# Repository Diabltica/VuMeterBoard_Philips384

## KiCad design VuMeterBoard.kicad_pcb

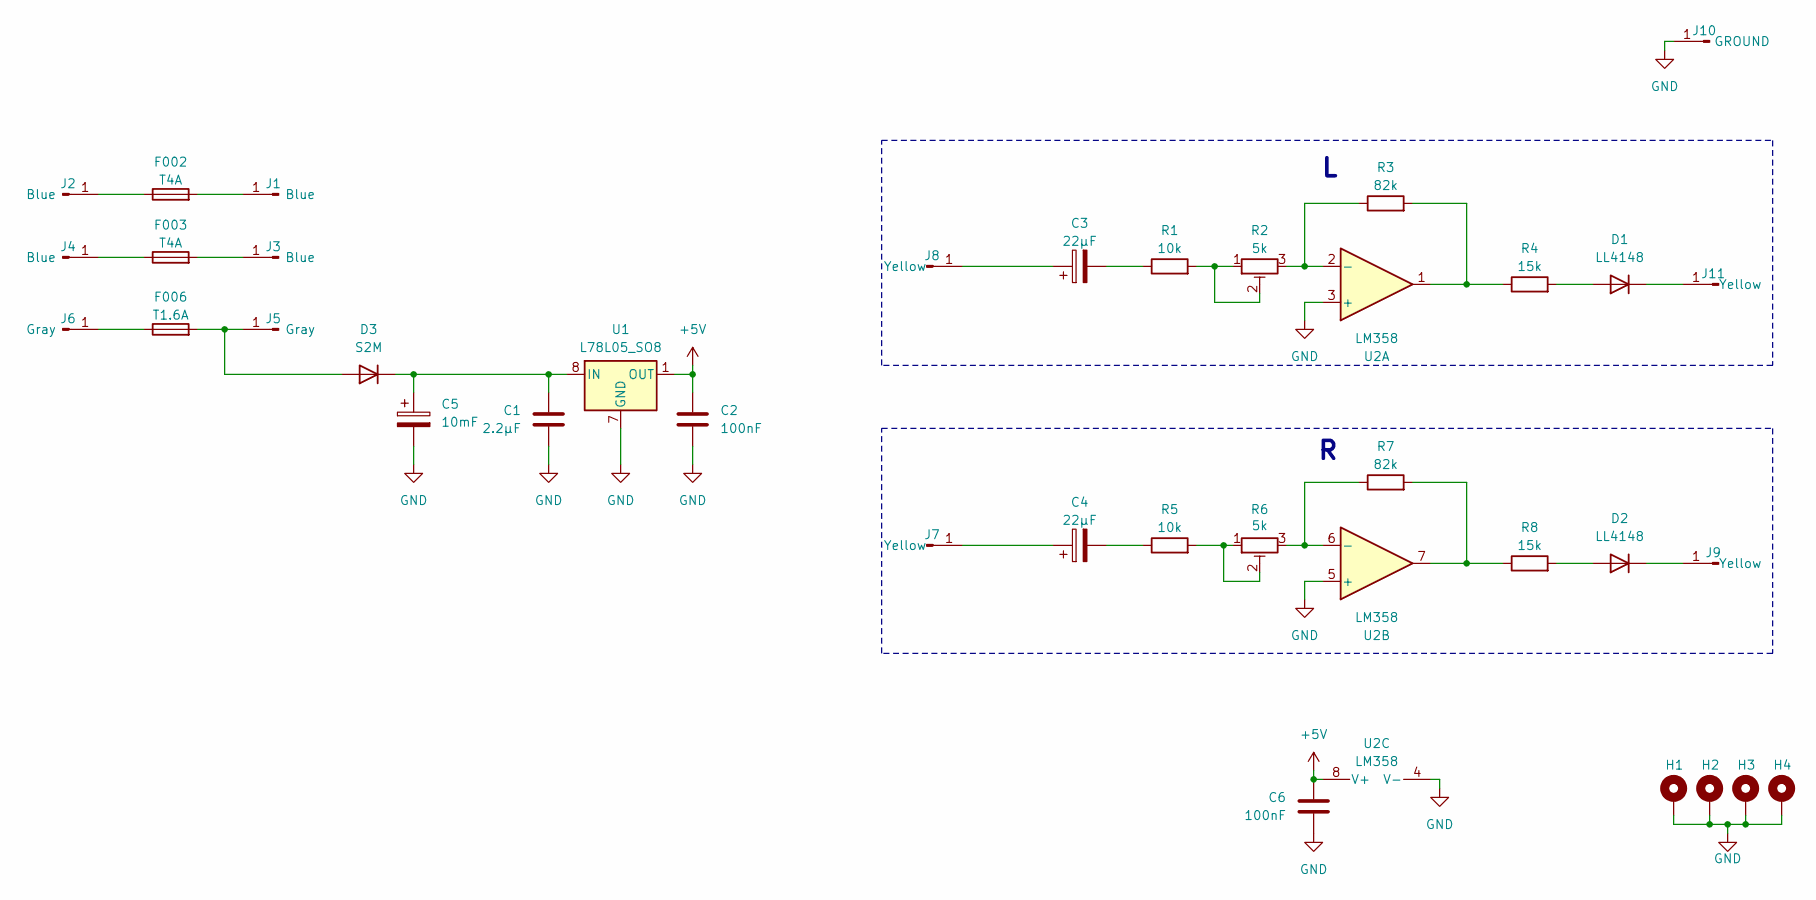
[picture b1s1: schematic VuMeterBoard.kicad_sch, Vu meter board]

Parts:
C1: 2.2µF; C_0603_1608Metric
C2, C6: 100nF; C_0603_1608Metric
C3, C4: 22µF; CP_Elec_6.3x7.7
C5: 10mF; CP_Radial_D18.0mm_P7.50mm
D1, D2: LL4148; D_MiniMELF
D3: S2M; D_SMB
F002, F003: T4A; Fuseholder_Cylinder-5x20mm_Stelvio-Kontek_PTF78_Horizontal_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
F006: T1.6A; Fuseholder_Cylinder-5x20mm_Stelvio-Kontek_PTF78_Horizontal_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
H1, H2, H3, H4: MountingHole_Pad; MountingHole_3.2mm_M3_Pad_Via
J1, J2, J3, J4, J5, J6, J7, J8, J9, J10, J11: Conn_01x01_Pin; PinHeader_1x01_P2.54mm_Vertical
R1, R5: 10k; R_0603_1608Metric
R2, R6: 5k; Potentiometer_Vishay_TS53YL_Vertical
R3, R7: 82k; R_0603_1608Metric
R4, R8: 15k; R_0603_1608Metric
U1: L78L05_SO8; SOIC-8_3.9x4.9mm_P1.27mm
U2: LM358; SOIC-8_3.9x4.9mm_P1.27mm

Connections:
+5V: C2.1, C6.1, U1.1 (OUT), U2.8 (V+)
GND: C1.2, C2.2, C5.2, C6.2, H1.1, H2.1, H3.1, H4.1, J10.1, U1.2 (GND), U1.3 (GND), U1.6 (GND), U1.7 (GND), U2.3 (+), U2.4 (V-), U2.5 (+)
unnamed: C3.2, R1.1
unnamed: C4.2, R5.1
unnamed: D1.2 (A), R4.2
unnamed: D1.1 (K), J11.1
unnamed: D2.2 (A), R8.2
unnamed: D2.1 (K), J9.1
unnamed: D3.2 (A), F006.2, J5.1
unnamed: C1.1, C5.1, D3.1 (K), U1.8 (IN)
unnamed: F002.2, J1.1
unnamed: F002.1, J2.1
unnamed: F003.2, J3.1
unnamed: F003.1, J4.1
unnamed: F006.1, J6.1
unnamed: C4.1, J7.1
unnamed: C3.1, J8.1
unnamed: R1.2, R2.1, R2.2
unnamed: R3.2, R4.1, U2.1
unnamed: R5.2, R6.1, R6.2
unnamed: R7.2, R8.1, U2.7
unnamed: R2.3, R3.1, U2.2 (-)
unnamed: R6.3, R7.1, U2.6 (-)

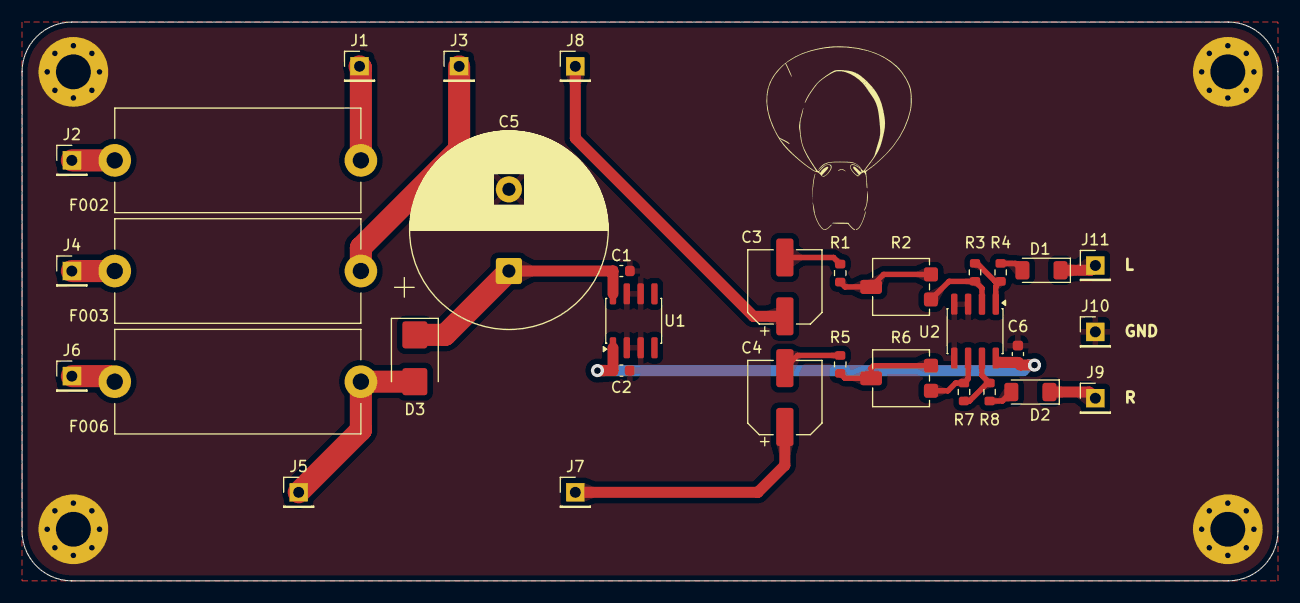
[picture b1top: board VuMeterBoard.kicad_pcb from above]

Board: 2 copper layers, 115.3 x 51.3 mm, 38 parts (0 on the bottom side), 23 nets.

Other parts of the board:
Frog**: Frog

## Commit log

2025-12-21 Add Licence
2025-12-21 create kicad project
2026-01-22 push file
